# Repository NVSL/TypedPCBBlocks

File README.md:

# TypedPCBBlocks
Typed PCB Blocks for ultra fast PCB Generation.

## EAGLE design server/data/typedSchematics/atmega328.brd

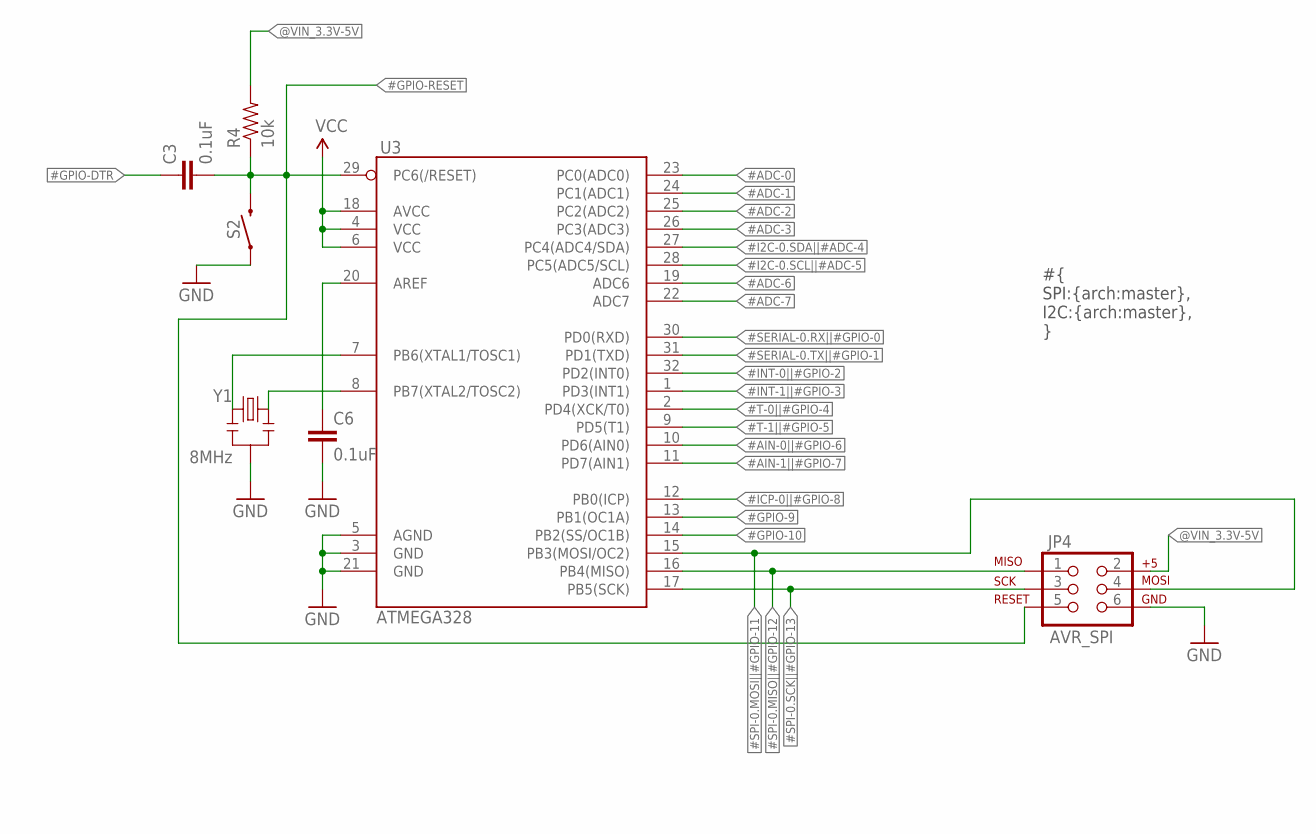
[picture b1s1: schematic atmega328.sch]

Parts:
C3, C6: 0.1uF; 0603
JP4: AVR_SPI; 2X3
R4: 10k; 0603
S2: MOMENTARY-SWITCH-SPST-SMD-6.2MM-TALL; TACTILE_SWITCH_SMD_6.2MM_TALL
U3: ATMEGA328; TQFP32-08
Y1: 8MHz; RESONATOR-SMD

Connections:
#ADC-0!: U3.23 (PC0(ADC0))
#ADC-1!: U3.24 (PC1(ADC1))
#ADC-2!: U3.25 (PC2(ADC2))
#ADC-3!: U3.26 (PC3(ADC3))
#ADC-6!: U3.19 (ADC6)
#ADC-7!: U3.22 (ADC7)
#GPIO-2!: U3.32 (PD2(INT0))
#GPIO-3!: U3.1 (PD3(INT1))
#GPIO-4!: U3.2 (PD4(XCK/T0))
#GPIO-5!: U3.9 (PD5(T1))
#GPIO-6!||#AIN-0!: U3.10 (PD6(AIN0))
#GPIO-7!||#AIN-1!: U3.11 (PD7(AIN1))
#GPIO-8!: U3.12 (PB0(ICP))
#GPIO-9!: U3.13 (PB1(OC1A))
#GPIO-10!: U3.14 (PB2(SS/OC1B))
#GPIO-DTR!: C3.1
#GPIO-RESET!: C3.2, JP4.5, R4.1, S2.B2 (2), U3.29 (PC6(/RESET))
#I2C-0.SCL!||#ADC-5!: U3.28 (PC5(ADC5/SCL))
#I2C-0.SDA!||#ADC-4!: U3.27 (PC4(ADC4/SDA))
#SERIAL-0.RX!||#GPIO-0!: U3.30 (PD0(RXD))
#SERIAL-0.TX!||#GPIO-1!: U3.31 (PD1(TXD))
#SPI-0.MISO!||#GPIO-12!: JP4.1, U3.16 (PB4(MISO))
#SPI-0.MOSI!||#GPIO-11!: JP4.4, U3.15 (PB3(MOSI/OC2))
#SPI-0.SCK!||#GPIO-13!: JP4.3, U3.17 (PB5(SCK))
@VIN_3.3V-5V: JP4.2, R4.2
AREF: C6.1, U3.20 (AREF)
GND: C6.2, JP4.6, S2.A2 (1), U3.3 (GND), U3.5 (AGND), U3.21 (GND), Y1.2
unnamed: U3.7 (PB6(XTAL1/TOSC1)), Y1.3
unnamed: U3.8 (PB7(XTAL2/TOSC2)), Y1.1
VCC: U3.4 (VCC), U3.6 (VCC), U3.18 (AVCC)

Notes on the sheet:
#{ SPI:{arch:master}, I2C:{arch:master}, }

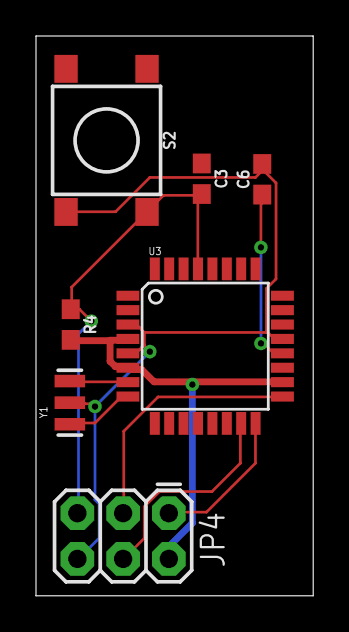
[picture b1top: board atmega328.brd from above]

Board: 2 copper layers, 15.4 x 31.1 mm, 7 parts (0 on the bottom side), 10 nets.

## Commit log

2021-06-08 Adding Nodes UI
2021-10-15 Moving files to folder
2021-10-15 firstCommit -schematicToTyped
2021-10-15 Adding schematic fixtures
2021-10-26 Improve fixtures
2021-10-26 Typed Schematic to JSON
2021-10-28 Adding support for range and list of voltages
2021-10-29 Adding Python Tuples format anotation in sch
2021-11-02 Cleaning json output format
2021-11-04 Adding ATMEGA328 Example
2021-11-05 Adding Typed Atmega328
2021-11-05 Adding support for multiple protocols in same net
2021-11-08 Improving typed schematics
2021-11-08 Adding ALTNAMES support to typed info
2021-11-09 Rename
2021-11-09 Fix repeated net name
2021-11-09 Adding typed schematics merger
2021-11-10 Adding untracked schematics
2021-11-10 Adding more merger code
2021-11-10 Adding test for connecting nets
2021-11-11 Removing initial sheet form empty sch template
2021-11-11 Schematic merger now working 🥳
2021-11-12 Adding reserved nets
2021-11-12 Adding brd files to test board merger
2021-11-13 Adding support for multiple same schematics
2021-11-16 Adding support for multiple sch instances
2021-11-16 Starting board block design transfer
2021-11-16 Fix unruted wire
2021-11-17 Moving dataflow program to old
2021-11-17 Workspace plumbing: yarn, eslint, prettier, ...
2021-11-17 Typed schematic connections plumbing
2021-11-17 Starting pin connection test
2021-11-17 Adding EAGLE output ignores
2021-11-18 Adding vscode workspace configs
2021-11-18 Allow import/exports for modules
2021-11-18 Adding dynamic imports for protocol defs
2021-11-18 Adding protocols base classes and implementatios
2021-11-18 Adding SPI class protocol
2021-11-19 Demo fixes
2021-11-20 Refactor folders, removing src
2021-11-20 Refactor server folder
2021-11-20 Adding xml2js
2021-11-20 Moving parser from python to typescript
2021-11-23 Finished parser prototype
2021-11-23 Redefining typed annotation
2021-11-23 Adding flash SPI schematic
2021-11-23 Improving makeConnections to support Array
2021-11-23 Adding parent to multiple childs connecitons
2021-11-24 Adding some SPI constrains
2021-11-24 Adding Relaxed JSON
2021-11-24 Adding example for text annotations
2021-11-24 Adding text annotations relaxed json parser
2021-11-25 Adding master-slave constrain to SPI
2021-11-25 adding power mats Tree portotype
2021-11-25 Adding typescript client UI
2021-11-30 Adding power Mat hasMap and Tree structure
2021-12-01 Fixed uuid to make them unique
2021-12-01 Adding typed power schematics
2021-12-02 Rename sch
2021-12-02 Adding voltage I/O parser
2021-12-02 Adding better voltage interface in parser
2021-12-02 Stariting power mats and typed sch integration
2021-12-03 Fix voltage ranges
2021-12-03 Adding get Vin Vout
2021-12-03 Adding voltages check for adding Mats on Tree
2021-12-07 Only one VIN allowed per power tsch
2021-12-07 Remove VIN for power connector
2021-12-07 Add typed power
2021-12-07 Only one VIN per tsch
2021-12-07 Adding add tsch to mats function
2021-12-10 Adding tschEDA Class
2021-12-10 Move tsch utils to tschEDA
2021-12-10 Adding tschEDA example
2022-01-06 Remove propagated vars
2022-01-06 Adding voltage source comparison in protocol connections
2022-01-07 Add filename to tsch
2022-01-07 prepare generate Json output
2022-01-10 Adding Json output
2022-01-11 Fixing generateJson output
2022-01-11 Adding tscheda output example
2022-01-12 Adding Queue Class for MatNodes
2022-01-12 Adding BFS for MatNodes
2022-01-13 Adding getVout with protocol key
2022-01-13 Adding voltage connections to json output
2022-01-14 Replace newMat & addMat parameters to uuids
2022-01-14 Refactoring
2022-01-14 Adding typedConstrants path in class | refactor
2022-01-15 Adding Multi-Key Hash Map
2022-01-18 Fix to multi-key hashmap
2022-01-18 Adding logger with verbose level
2022-01-18 Cleanning logs and Multi-key maps
2022-01-18 Adding output files by design name
2022-01-18 Adding Led output example
2022-01-18 Adding GPIO Constraints
2022-01-18 Adding LED TschEDA example
2022-01-18 FIx Tsch's with no VIN (e.g., LED)
2022-01-18 Compile all contraints by default
2022-01-19 Better error handling
2022-01-19 Adding MCP9808 I2C example
2022-01-19 Adding 12C constraints
2022-01-19 Fix output file
2022-01-19 Adding I2C options in schematic + Voltage fix
2022-01-20 Adding three error handling styles :)
2022-01-21 Small refactor
2022-01-22 Adding Error Codes
2022-01-22 Adding better error handling
2022-01-22 Adding error handling for dynamic contrants
2022-01-22 Modifing examples to support error handling
2022-01-25 Outputs with required symbol
2022-01-25 Adding required annotation symbol
2022-01-25 Adding support for required annotation
2022-01-25 Adding Desing Rule Checks
2022-01-25 Adding design rule check error
2022-01-25 Adding drc to main example
2022-01-26 New Outputs with require
2022-01-26 Schematics with require annotation
2022-01-26 Full examples with require annotation
2022-01-28 Refactoring server tscheda api into a package
2022-01-28 Removing tscheda api from server
2022-01-28 Adding global monorepo scripts
2022-01-28 Improving server scripts
2022-01-28 Fix deleted server main
2022-01-28 Adding connection map info as class method
2022-02-03 Removing TODOs
2022-02-03 Adding client start and build scripts
2022-02-03 😨XMLjs doesn't work in browser, breaks everything
2022-02-04 Removing test code
2022-02-04 Remove node pllify
2022-02-04 Adding schematics and constraints for web client
2022-02-04 Refactor server data
2022-02-04 Refactor Tsch EDA library
2022-02-04 Refactor server and client
2022-02-08 Adding Schema Flow First Commit
2022-02-08 Adding Schema Flow CSS
2022-02-08 Adding SchemaFlow Example
2022-02-09 Adding one more node example
2022-02-09 Contnuing JS to TS conversion.
2022-02-10 Continuing JS to TS migration plus improvements.
2022-02-11 IImporoveing delete node and node connections
2022-02-15 Adding remove node and node connections
2022-02-15 Fix CSS
2022-02-15 Trying out interactjs for drag and drop
2022-02-16 Continue Library testing for Mat block
2022-02-17 Adding restricted sizing to inner blocks
2022-02-18 Continuing expermenting
2022-02-19 Fixing HTML
2022-02-19 Moving tschEda example to another file
2022-02-19 Adding context menu and zIndex UP/Down
2022-02-24 Add layer context menu to any tsch element
2022-02-24 Fix elements moved when resizing
2022-02-24 Clean CSS before Merge
2022-02-24 Clean HTML before Merge
2022-02-24 Clean TS Before Merge
2022-02-25 Clean TS
2022-02-25 Add mat drop background
2022-02-26 Adding dragging for all objects inside mats.
2022-03-01 Moving Mat Code to a Class
2022-03-01 Refactor
2022-03-01 Remove console logs
2022-03-01 Add htmlContainerTag in Constructor
2022-03-01 Refactor html tags
2022-03-02 Starting Integration (Mat+Nodes)
2022-03-03 Continuing (MAT-Nodes) integration, CSS
2022-03-03 Continuing (MAT-Nodes) integration, TS
2022-03-04 Adding svg Connectons to integration
2022-03-05 Adding Connection Mapping Interfaces
2022-03-08 Adding node Connections
2022-03-08 Test SVG defs
2022-03-09 Remove SVG Test
2022-03-09 Adding svg defs, Fix connection bug, drag bug
2022-03-09 Adding update All Nodes, and svg markers
2022-03-10 Cleaning code of logs.
2022-03-11 Adding Context Menus
2022-03-11 Adding context menus, fix resize/drag
2022-03-11 Fix postion at connect
2022-03-12 Starting Delete Elements integration
2022-03-15 Fix connection select
2022-03-15 Add nodes and connections delete
2022-03-16 Big Refactor | Moving code to separate files
2022-03-17 Fix refactoring exports issue
2022-03-17 Fix node inputs
2022-03-17 Fix delete node input/outpus
2022-03-17 Adding two-way connections
2022-03-17 Fixing two-way connections curvature
2022-03-18 Add and rename utils
2022-03-18 Continuing with refactoring
2022-03-23 Adding ability to change IOs Left or Right
2022-03-25 Fix no delete connection bug
2022-03-25 Fix no connection created after left|right
2022-03-25 Adding net positions and configs to tscheda lib
2022-03-25 TschedaFlow first commit
2022-03-25 Adding Utils functions to TschedaFlow
2022-03-25 Changing example to us use TschedaFlow
2022-03-26 Continuing integration of UI with Tsch Lib
2022-03-29 Fix css text wrap
2022-03-29 Adding altname
2022-03-29 Adding extrainfo property for BlockType info
2022-03-29 Adding BlockTypes
2022-03-29 Configuring schematics with blocktype info
2022-03-31 Adding Mat Tsch to UI
2022-04-05 Adding isMatRoot func
2022-04-05 Adding support for uuids
2022-04-05 Addng events disptacher
2022-04-11 Prevent multiple connections of the same
2022-04-11 Adding Mat-Drop getter & setter
2022-04-11 Adding Drop, Unddrop & Connect events to parent
2022-04-12 Adding Drop event info types
2022-04-13 Adding get block type
2022-04-13 Prevent double undrop
2022-04-13 Improving flow drop event
2022-04-13 Adding rever block position
2022-04-13 Adding Connect Event Info Interface
2022-04-14 Adding connect/disconnect with dispatch event flow
2022-04-15 Adding control buttons
2022-04-15 Adding axios and server data
2022-04-15 Fix page space
2022-04-15 Adding sch gen integration beteween lib and UI
2022-04-15 Adding server with express and queries
2022-04-15 Fix merge schematic output path
2022-04-16 Adding generate schematic query
2022-04-16 Adding file-saver package
2022-04-16 File-saver and generate query integration
2022-04-16 Update server side schematics
2022-04-19 Cleaning server side
2022-04-19 Cleaning main
2022-04-19 Refactoring paths
2022-04-19 Check z-indexes for drop and adding drop states
2022-04-19 Adding get zIndex
2022-04-20 Ignore merged schematic output
2022-04-21 Adding error Toast to UI
2022-04-21 Error Toast messages integration
2022-04-22 toastError integration with TschedaFlow
2022-04-22 Fix Tsch block's positions for testing
2022-04-22 Add toastError for DRC
2022-04-22 Fix I2C and SPI constraints msg errors
2022-04-22 Adding missing build constraints
2022-04-22 Fix Hashmap
2022-04-22 Fix from-to uuids
2022-04-22 Fixing multiple net connecitons map
2022-04-23 Clean logs
2022-04-23 Adding better connection status scheme
2022-04-26 Fixed GPIO contraints
2022-04-26 Adding GPIO altname for led typed schematic
2022-04-26 Adding warning if no server available
2022-04-26 Fixed connection alredy exists query selector
2022-04-26 Fixing connection Json generation & adding connection constraint
2022-04-26 Improve unique schematics prefix
2022-04-26 Adding json merge input example for py script
2022-04-27 Adding Flow Delete Event
2022-04-27 Refactor ConnectionData
2022-04-27 Adding delete event info to delete events
2022-04-28 Adding structuredClone for deep cloning
2022-04-28 Addin deep copy utils functions
2022-04-28 Print Mat Tree as well using BFS algorithm
2022-04-28 Switching delete from static to event driven
2022-04-28 Integrating delete to TschEDA + Flow UI
2022-04-29 Add generated uuid to Tsch class
2022-04-29 Add delete to MultiKey Hasmap class
2022-04-29 Adding delete routines to Tsch Lib
2022-05-05 Fix, delete connection when removing node
2022-05-05 Adding Tsch deletion in TschEda, fix mat's delete
2022-05-05 Deprecate raw connection
2022-05-05 Adding delete connections integration
2022-05-05 Fix deletion order
2022-05-05 Change error msg
2022-05-06 Adding remove all node connections
2022-05-06 Adding get mat element
2022-05-06 Adding error cases
2022-05-06 Implementing undrop (remove from design)
2022-05-06 Undrop integration
2022-06-02 Move app css to main
2022-06-02 Beutify Typed Schematic Blocks for paper
2022-07-19 Adding bulma
2022-07-19 Adding Bulma NavBar
2022-07-19 Fix TSch CSS specifity conflict with Bulma CSS
2022-07-20 Adding CSS flex panels
2022-07-20 Fix CSS input output selector cz bulma integration
2022-07-20 Fix CSS progress selector cz bulma integration
2022-07-21 Adding schematic blocks side panel
2022-07-21 Side Panels CSS
2022-07-22 Fix null target Elements.
2022-07-22 Refactor IO tag
2022-07-22 Styling side panel
2022-07-23 Adding drag/drop blocks
2022-07-27 Adding NavBarurger open/close
2022-07-28 Improving Side Panel
2022-07-29 Adding schematic images
2022-07-29 Clean
2022-07-29 Adding images hardcoded path
2022-07-30 Adding images & functionality to side panel.

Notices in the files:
parts and their libraries:
SparkFun-Resistors: Licensing: Creative Commons ShareAlike 4.0 International - https://creativecommons.org/licenses/by-sa/4.0
